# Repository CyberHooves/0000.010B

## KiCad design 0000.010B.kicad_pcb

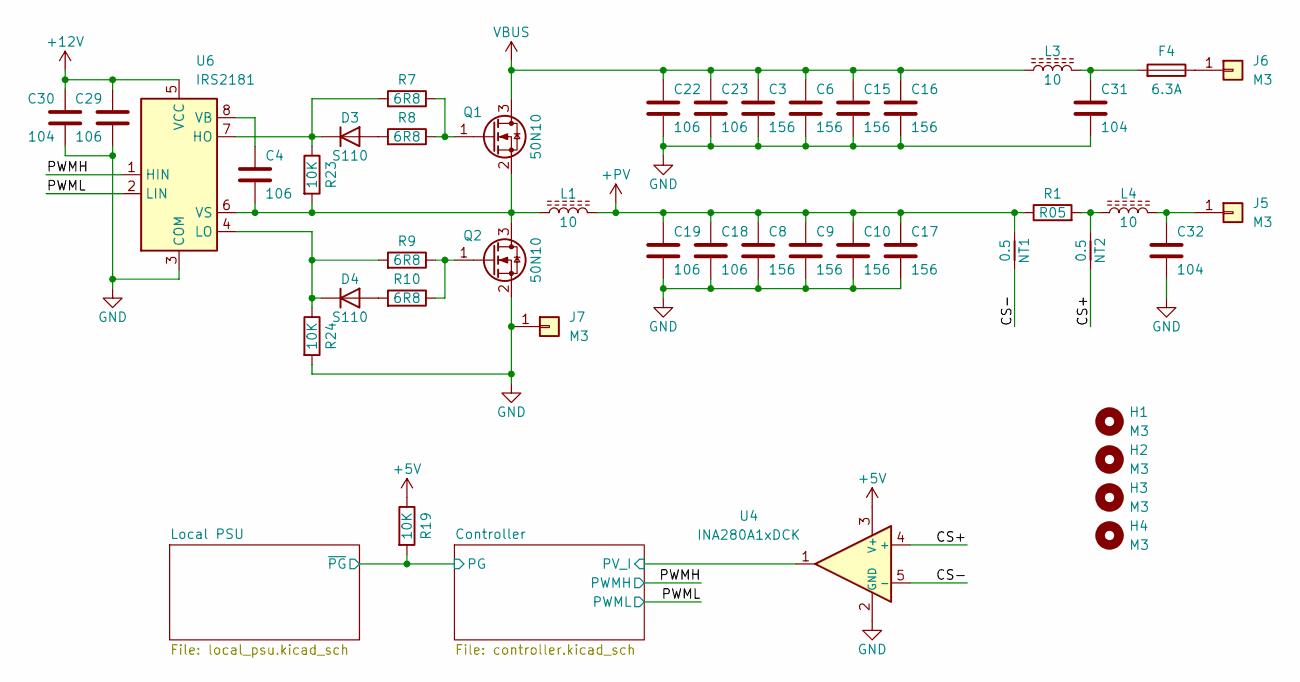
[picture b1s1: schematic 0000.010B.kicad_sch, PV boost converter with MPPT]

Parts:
C3, C6, C8, C9, C10, C15, C16, C17: 156; C_2220_5750Metric
C4, C18, C19, C22, C23, C29: 106; C_1210_3225Metric
C30: 104; C_0805_2012Metric
C31, C32: 104; C_1206_3216Metric
D3, D4: S110; D_SOD-123
F4: 6.3A; Fuse_Schurter_UMT250
H1, H2, H3, H4: M3; MountingHole_3.2mm_M3
J5, J6, J7: M3; MountingHole_3.2mm_M3_Pad
L1: 10; L_Vishay_IHLP-6767
L3, L4: 10; L_SMD_7x7
NT1, NT2: 0.5; NetTie-2_SMD_Pad0.5mm
Q1, Q2: 50N10; TO-252-2
R1: R05; R_2512_6332Metric
R7, R8, R9, R10: 6R8; R_1206_3216Metric
R19, R23, R24: 10K; R_0805_2012Metric
U4: INA280A1xDCK; SOT-23-5
U6: IRS2181; SOIC-8_3.9x4.9mm_P1.27mm

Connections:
+5V: R19.1, U4.3 (V+); also elsewhere on the board
+12V: C29.1, C30.1, U6.5 (VCC); also elsewhere on the board
+PV: C8.1, C9.1, C10.1, C17.1, C18.1, C19.1, L1.2, NT1.1, R1.1; also elsewhere on the board
/CS+: NT2.2, U4.4 (+)
/CS-: NT1.2, U4.5 (-)
/Controller/PG: R19.2; also elsewhere on the board
/Controller/PV_I: U4.1; also elsewhere on the board
/PWMH: U6.1 (HIN); also elsewhere on the board
/PWML: U6.2 (LIN); also elsewhere on the board
GND: C3.2, C6.2, C8.2, C9.2, C10.2, C15.2, C16.2, C17.2, C18.2, C19.2, C22.2, C23.2, C29.2, C30.2, C31.2, C32.2, J7.1 (Pin_1_1), Q2.2 (S), R24.2, U4.2 (GND), U6.3 (COM); also elsewhere on the board
unnamed: C31.1, F4.2, L3.2
unnamed: D3.2 (A), R8.2
unnamed: D3.1 (K), R7.2, R23.1, U6.7 (HO)
unnamed: D4.2 (A), R10.2
unnamed: D4.1 (K), R9.2, R24.1, U6.4 (LO)
unnamed: C32.1, J5.1 (Pin_1_1), L4.2
unnamed: F4.1, J6.1 (Pin_1_1)
unnamed: L4.1, NT2.1, R1.2
unnamed: Q1.1 (G), R7.1, R8.1
unnamed: C4.2, L1.1, Q1.2 (S), Q2.3 (D), R23.2, U6.6 (VS)
unnamed: Q2.1 (G), R9.1, R10.1
unnamed: C4.1, U6.8 (VB)
VBUS: C3.1, C6.1, C15.1, C16.1, C22.1, C23.1, L3.1, Q1.3 (D); also elsewhere on the board

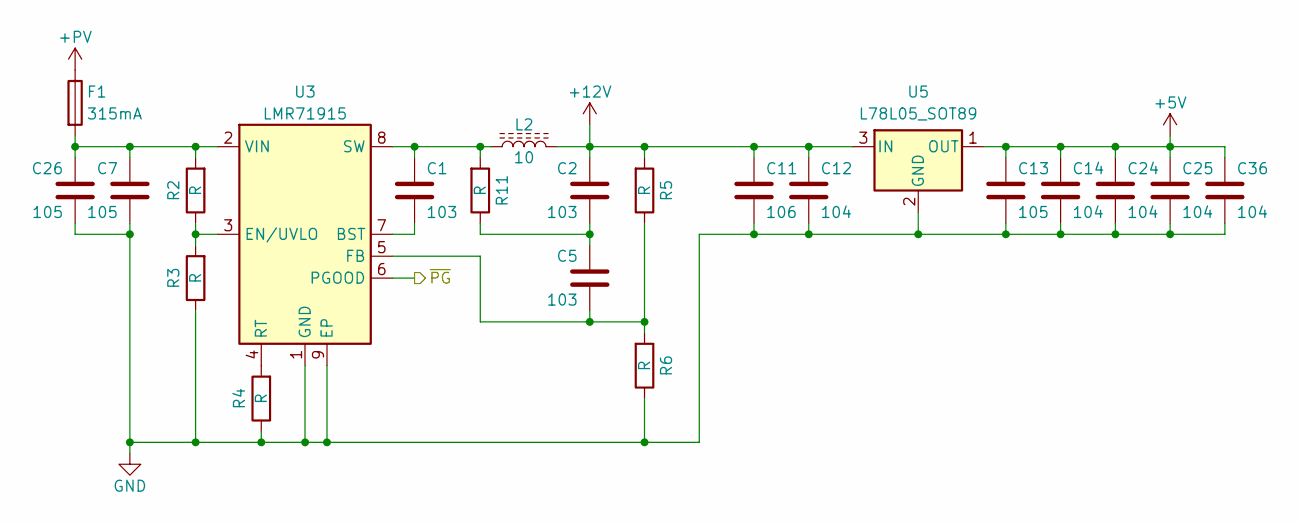
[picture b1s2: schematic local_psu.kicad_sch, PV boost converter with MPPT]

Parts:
C1, C2, C5: 103; C_0805_2012Metric
C7, C26: 105; C_1210_3225Metric
C11: 106; C_1210_3225Metric
C12, C14, C24, C25, C36: 104; C_0805_2012Metric
C13: 105; C_0805_2012Metric
F1: 315mA; FUSE_2410_6125Metric
L2: 10; L_SMD_5x5
R2, R3, R4, R5, R6, R11: R; R_0805_2012Metric
U3: LMR71915; SOIC-8-1EP_3.9x4.9mm_P1.27mm_EP2.514x3.2mm
U5: L78L05_SOT89; SOT-89-3

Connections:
+5V: C13.1, C14.1, C24.1, C25.1, C36.1, U5.1 (OUT); also elsewhere on the board
+12V: C2.1, C11.1, C12.1, L2.2, R5.2, U5.3 (IN); also elsewhere on the board
+PV: F1.1; also elsewhere on the board
/Controller/PG: U3.6 (PGOOD); also elsewhere on the board
GND: C7.2, C11.2, C12.2, C13.2, C14.2, C24.2, C25.2, C26.2, C36.2, R3.1, R4.1, R6.1, U3.1 (GND), U3.9 (EP), U5.2 (GND); also elsewhere on the board
unnamed: C2.2, C5.1, R11.1
unnamed: C1.2, U3.7 (BST)
unnamed: R2.1, R3.2, U3.3 (EN/UVLO)
unnamed: C5.2, R5.1, R6.2, U3.5 (FB)
unnamed: R4.2, U3.4 (RT)
unnamed: C1.1, L2.1, R11.2, U3.8 (SW)
unnamed: C7.1, C26.1, F1.2, R2.2, U3.2 (VIN)

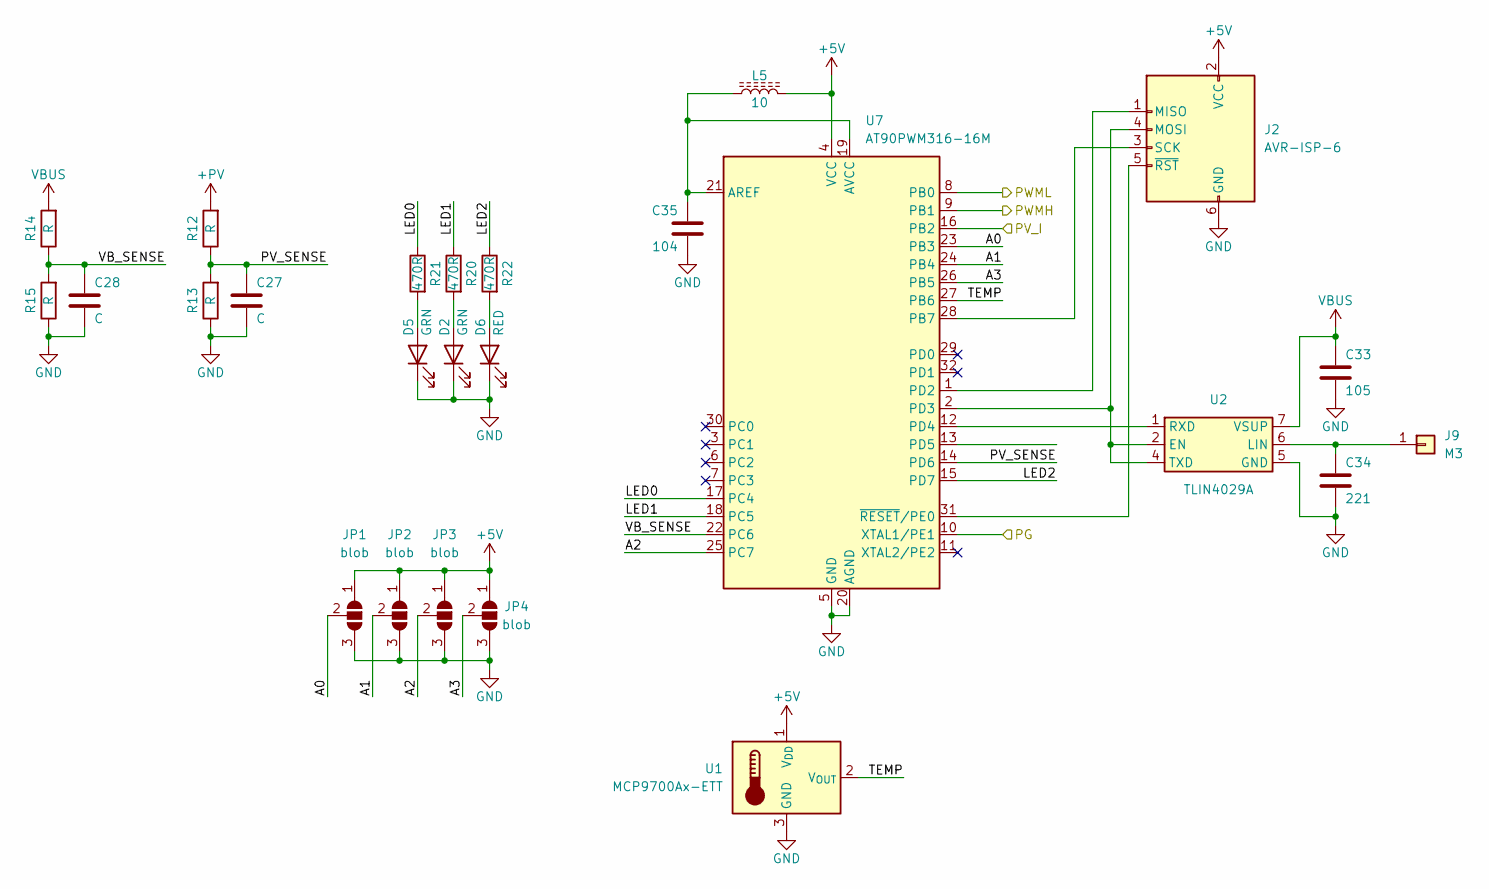
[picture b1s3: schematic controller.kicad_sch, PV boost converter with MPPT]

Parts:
C27, C28: C; C_0805_2012Metric
C33: 105; C_0805_2012Metric
C34: 221; C_0805_2012Metric
C35: 104; C_0805_2012Metric
D2, D5: GRN; LED_0805_2012Metric
D6: RED; LED_0805_2012Metric
J2: AVR-ISP-6; PinHeader_2x03_P2.54mm_Vertical_SMD
J9: M3; MountingHole_3.2mm_M3_Pad
JP1, JP2, JP3, JP4: blob; SolderJumper-3_P1.3mm_Open_RoundedPad1.0x1.5mm
L5: 10; L_0805_2012Metric
R12, R14: R; R_1206_3216Metric
R13, R15: R; R_0805_2012Metric
R20, R21, R22: 470R; R_0805_2012Metric
U1: MCP9700Ax-ETT; SOT-23
U2: TLIN4029A; SOIC-8_3.9x4.9mm_P1.27mm
U7: AT90PWM316-16M; QFN-32-1EP_7x7mm_P0.65mm_EP4.65x4.65mm

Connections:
+5V: J2.2 (VCC), JP1.1 (A), JP2.1 (A), JP3.1 (A), JP4.1 (A), L5.2, U1.1 (V_{DD}), U7.4 (VCC); also elsewhere on the board
+PV: R12.2; also elsewhere on the board
/Controller/A0: JP1.2 (C), U7.23 (PB3)
/Controller/A1: JP2.2 (C), U7.24 (PB4)
/Controller/A2: JP3.2 (C), U7.25 (PC7)
/Controller/A3: JP4.2 (C), U7.26 (PB5)
/Controller/LED0: R21.1, U7.17 (PC4)
/Controller/LED1: R20.1, U7.18 (PC5)
/Controller/LED2: R22.1, U7.15 (PD7)
/Controller/PG: U7.10 (XTAL1/PE1); also elsewhere on the board
/Controller/PV_I: U7.16 (PB2); also elsewhere on the board
/Controller/PV_SENSE: C27.1, R12.1, R13.2, U7.14 (PD6)
/Controller/TEMP: U1.2 (V_{OUT}), U7.27 (PB6)
/Controller/VB_SENSE: C28.1, R14.1, R15.2, U7.22 (PC6)
/PWMH: U7.9 (PB1); also elsewhere on the board
/PWML: U7.8 (PB0); also elsewhere on the board
GND: C27.2, C28.2, C33.2, C34.2, C35.2, D2.1 (K), D5.1 (K), D6.1 (K), J2.6 (GND), JP1.3 (B), JP2.3 (B), JP3.3 (B), JP4.3 (B), R13.1, R15.1, U1.3 (GND), U2.5 (GND), U7.5 (GND), U7.20 (AGND), U7.33 (GND); also elsewhere on the board
unnamed: D2.2 (A), R20.2
unnamed: D5.2 (A), R21.2
unnamed: D6.2 (A), R22.2
unnamed: J2.1 (MISO), U7.1 (PD2)
unnamed: J2.4 (MOSI), U2.2 (EN), U2.4 (TXD), U7.2 (PD3)
unnamed: J2.3 (SCK), U7.28 (PB7)
unnamed: J2.5 (~RST), U7.31 (~RESET/PE0)
unnamed: C34.1, J9.1 (Pin_1_1), U2.6 (LIN)
unnamed: U2.1 (RXD), U7.12 (PD4)
unnamed: C35.1, L5.1, U7.19 (AVCC), U7.21 (AREF)
VBUS: C33.1, R14.2, U2.7 (VSUP); also elsewhere on the board

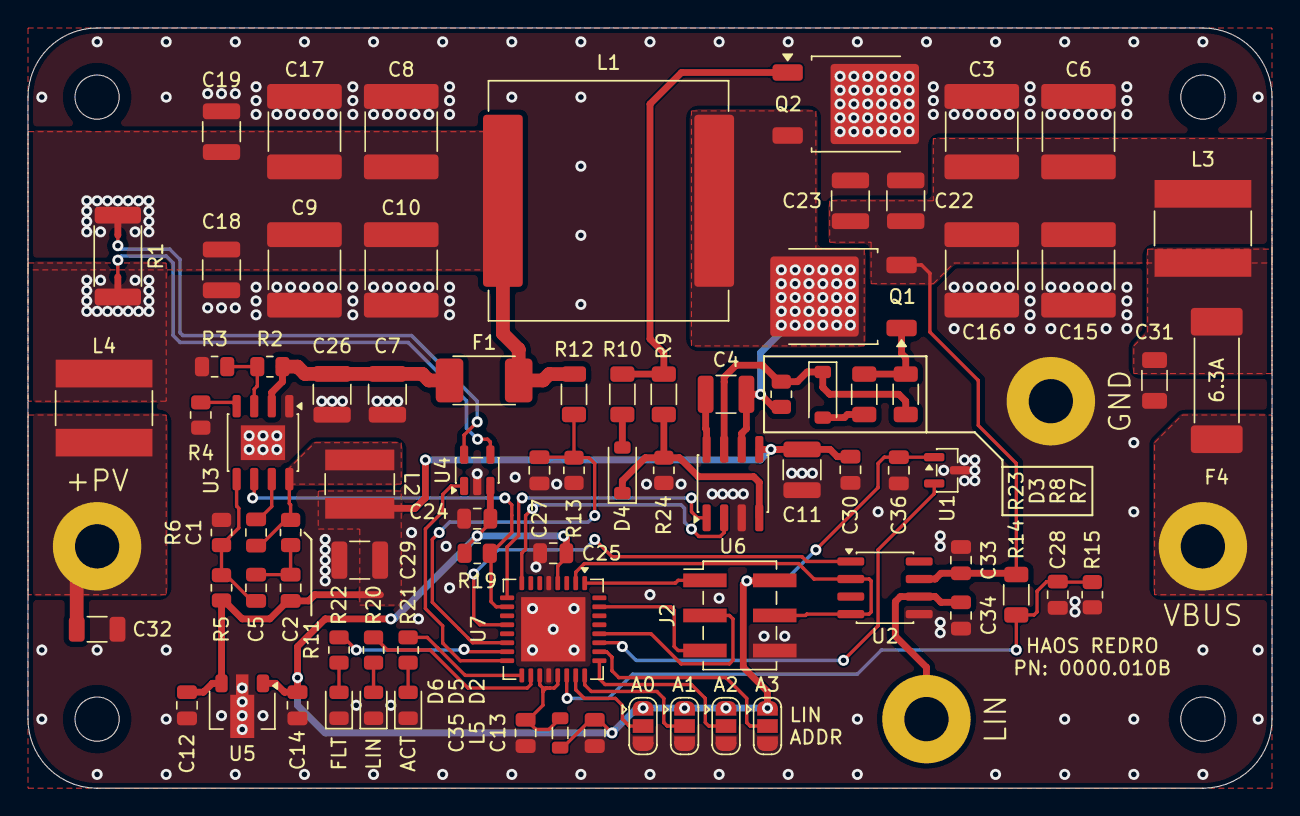
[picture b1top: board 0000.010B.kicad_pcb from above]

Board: 2 copper layers, 90.0 x 55.0 mm, 91 parts (0 on the bottom side), 50 nets.

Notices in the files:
0000.010B.kicad_pcb:
Released under CERN OHL 2.0-S
Copyright Taiyo Rawle 2026
